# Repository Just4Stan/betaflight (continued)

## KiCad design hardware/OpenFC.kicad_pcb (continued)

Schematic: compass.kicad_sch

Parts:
C113: 100n; C_0402_1005Metric; LCSC C1525; not fitted
U31: LIS3MDLTR; LGA-12_L2.0-W2.0-P0.50-BL; LCSC Part C478483; not fitted

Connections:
unnamed: C113.1, U31.4 (C1), U31.5 (Vdd), U31.6 (Vdd_IO), U31.10 (CS)
unnamed: C113.2, U31.3 (GND), U31.9 (SD0/SA1)

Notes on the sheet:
Place far from magnetic interference sources

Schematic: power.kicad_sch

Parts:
C2, C16: 22uF; C_0402_1005Metric; LCSC C105226
C32, C33, C39: 100n; C_0402_1005Metric; LCSC C1525
C35, C37: 4.7uF 50v; C_0805_2012Metric; LCSC C98192
C36: 100nF; C_0402_1005Metric; LCSC C1525
C38, C40, C48: 22uF; C_0603_1608Metric; LCSC C2762594
D1, D4, D5, D7: LED_1_Green; LED_0603_1608Metric; LCSC C2994781
D3, D21: RB161QS-40_C28646385; SOD-882_L1.0-W0.6-RD; LCSC Part C28646385
L3, L4: XRTC303020D4R7MBCA; IND-SMD_L3.0-W3.0_AFE303020S; LCSC Part C39846837
Q1: DMN1150UFB-7B; DFN-3L_L1.0-W0.6-P0.65-BR; LCSC Part C459538
R4: 30R; R_0402_1005Metric; LCSC C138007
R7, R14, R16: 100k; R_0402_1005Metric; LCSC C60491
R8: 39k; R_0402_1005Metric; LCSC C137995
R12, R15: 200R; R_0402_1005Metric; LCSC C25087
R19: 10k; R_0402_1005Metric; LCSC C25087
R28: 5.23k; R_0402_1005Metric; LCSC C2684530
R29: 470; R_0402_1005Metric; LCSC C114877
R31: 13.7k; R_0402_1005Metric; LCSC C2933072
U6, U7: LMR51420YDDCR; SOT-23-6_L2.9-W1.6-P0.95-LS2.9-BL; LCSC Part C5383002
U13: TPS746-3.3DRV; WSON-6-1EP_2x2mm_P0.65mm_EP1x1.6mm; LCSC C2868202
U21: NCV8187AMT180TAG; WDFN-6_L2.0-W2.0-P0.65-BL-EP; LCSC Part C893189
U33: TPS2116DRLR; SOT-583-8_L2.1-W1.6-P0.50-LS1.6-BL; LCSC Part C3235557

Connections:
+1.8V_GYRO: C2.1, U21.5 (SNS), U21.6 (OUT); also elsewhere on the board
+3.3V: C16.1, R4.1, U13.1 (OUT); also elsewhere on the board
+5V: C32.1, C33.1, C48.1, D3.1 (C), R12.1, R19.1, U13.4 (EN), U13.6 (IN), U21.1 (IN), U21.2 (EN), U33.2 (VOUT), U33.7 (VOUT); also elsewhere on the board
+5V_BUCK: C40.1, D3.2 (A), L4.2, R7.1, R15.1, R16.2, U33.3 (VIN1), U33.5 (MODE); also elsewhere on the board
+5V_USB: U33.6 (VIN2); also elsewhere on the board
+12V: C38.1, L3.2, R14.2, R29.1; also elsewhere on the board
+BATT: C35.1, C37.1, D21.1 (C), U6.3 (VIN), U6.5 (EN), U7.3 (VIN), U7.5 (EN); also elsewhere on the board
/POWER/1.8V_PG: Q1.1 (G), R19.2, U21.4 (PG)
GND: C2.2, C16.2, C32.2, C33.2, C35.2, C37.2, C38.2, C40.2, C48.2, D1.1 (K), D4.1 (K), D5.1 (K), D21.2 (A), Q1.2 (S), R8.2, R28.2, R31.2, U6.1 (GND), U7.1 (GND), U13.3 (GND), U13.5 (PG), U13.7 (EP), U21.3 (GND), U21.7 (EP), U33.1 (GND); also elsewhere on the board
unnamed: D1.2 (A), R15.2
unnamed: D4.2 (A), R4.2
unnamed: D5.2 (A), R29.2
unnamed: D7.2 (A), R12.2
unnamed: D7.1 (K), Q1.3 (D)
unnamed: C36.2, U6.6 (CB)
unnamed: R14.1, R28.1, U6.4 (FB)
unnamed 103: C36.1, L3.1, U6.2 (SW); also elsewhere on the board
unnamed: C39.2, U7.6 (CB)
unnamed: R16.1, R31.1, U7.4 (FB)
unnamed 106: C39.1, L4.1, U7.2 (SW); also elsewhere on the board
unnamed: R7.2, R8.1, U33.4 (PR1)

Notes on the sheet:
10V
3.3V 1A LDO
1.8V 150mA LDO (high PSRR)
5V Power MUX
Switches up to 4A (TPS2117) from +5V_USB or +5V_BUCK to +5V. Prefers buck over USB, threshold voltage is about 3.5V. The threshold voltage is low to prevent accidental switchover to USB during peak consumption (worst case in flight). Emergency diode for if that happens during flight.

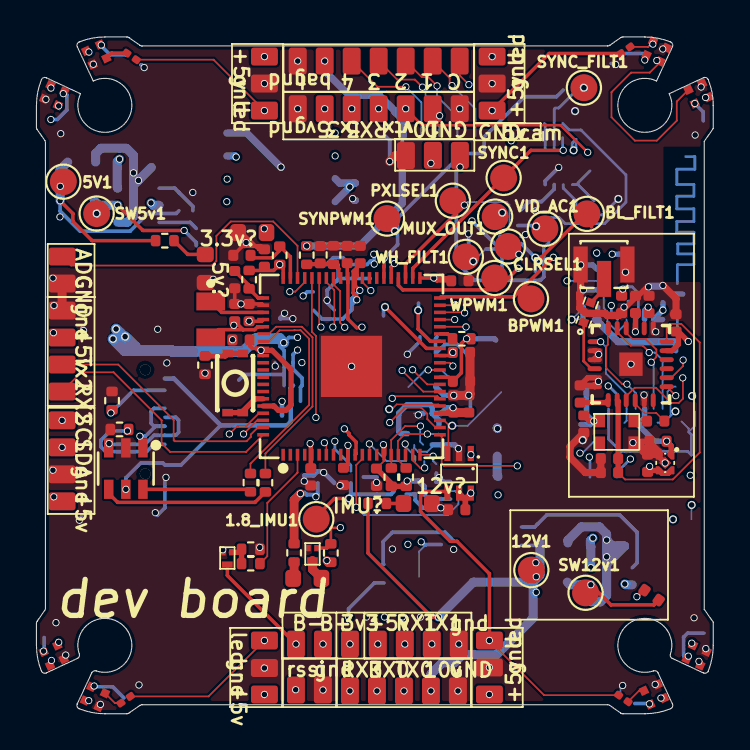
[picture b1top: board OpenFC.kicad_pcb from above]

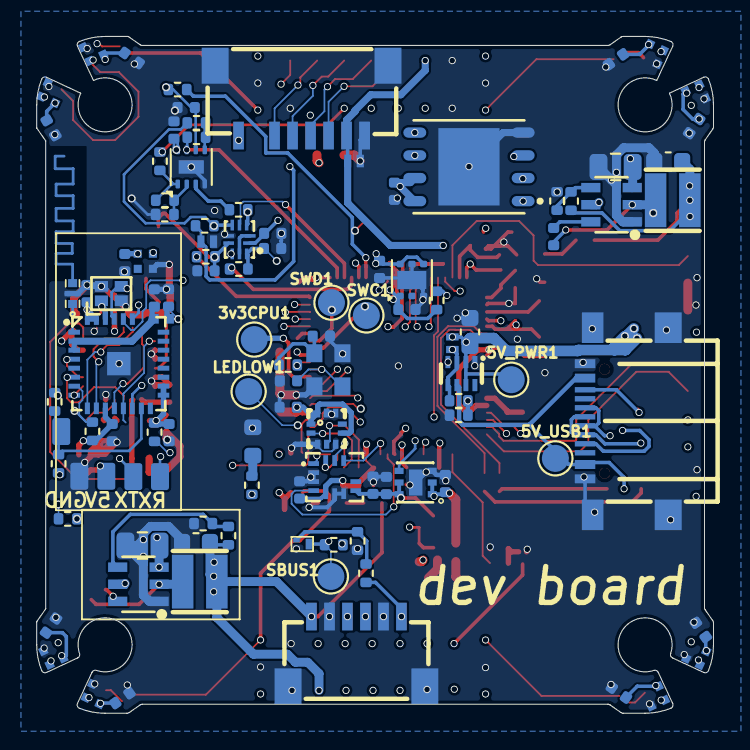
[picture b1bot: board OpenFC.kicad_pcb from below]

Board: 8 copper layers, 37.6 x 37.6 mm, 253 parts (108 on the bottom side), 131 nets.

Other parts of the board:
1.8_IMU1, 3v3CPU1, 5V1, 5V_PWR1, 5V_USB1, 12V1: TestPoint; TestPoint_Pad_D1.5mm
BL_FILT1: TestPoint; TestPoint_Pad_D1.5mm
BPWM1: TestPoint; TestPoint_Pad_D1.5mm
CLRSEL1: TestPoint; TestPoint_Pad_D1.5mm
LEDLOW1: TestPoint; TestPoint_Pad_D1.5mm
MUX_OUT1: TestPoint; TestPoint_Pad_D1.5mm
PXLSEL1: TestPoint; TestPoint_Pad_D1.5mm
SBUS1: TestPoint; TestPoint_Pad_D1.5mm
SW5v1, SW12v1: TestPoint; TestPoint_Pad_D1.5mm
SWC1: TestPoint; TestPoint_Pad_D1.5mm
SWD1: TestPoint; TestPoint_Pad_D1.5mm
SYNC1: TestPoint; TestPoint_Pad_D1.5mm
SYNC_FILT1: TestPoint; TestPoint_Pad_D1.5mm
SYNPWM1: TestPoint; TestPoint_Pad_D1.5mm
VID_AC1: TestPoint; TestPoint_Pad_D1.5mm
WH_FILT1: TestPoint; TestPoint_Pad_D1.5mm
WPWM1: TestPoint; TestPoint_Pad_D1.5mm

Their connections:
+1.8V_GYRO: 1.8_IMU1.1; also elsewhere on the board
+3.3V: 3v3CPU1.1; also elsewhere on the board
+5V: 5V_PWR1.1; also elsewhere on the board
+5V_BUCK: 5V1.1; also elsewhere on the board
+5V_USB: 5V_USB1.1; also elsewhere on the board
+12V: 12V1.1; also elsewhere on the board
/OSD/OSD_PIXSEL: PXLSEL1.1; also elsewhere on the board
/OSD/OSD_PIX_COLOR: CLRSEL1.1; also elsewhere on the board
/OSD/OSD_SYNCLVL_PWM: SYNPWM1.1; also elsewhere on the board
/OSD/OSD_SYNC_RAW: SYNC1.1; also elsewhere on the board
/OSD/OSD_VBLACK_PWM: BPWM1.1; also elsewhere on the board
/OSD/OSD_VWHITE_PWM: WPWM1.1; also elsewhere on the board
/OSD/VBLACK_FILT: BL_FILT1.1; also elsewhere on the board
/OSD/VID_IN: VID_AC1.1; also elsewhere on the board
/OSD/VID_MUX_OUT: MUX_OUT1.1; also elsewhere on the board
/OSD/VWHITE_FILT: WH_FILT1.1; also elsewhere on the board
/RP2350A/LED_STRIP_L: LEDLOW1.1; also elsewhere on the board
/RP2350A/SBUS_INVERT: SBUS1.1; also elsewhere on the board
unnamed 103: SW12v1.1; also elsewhere on the board
unnamed 106: SW5v1.1; also elsewhere on the board
unnamed 122: SWC1.1; also elsewhere on the board
unnamed 123: SWD1.1; also elsewhere on the board
unnamed 131: SYNC_FILT1.1; also elsewhere on the board

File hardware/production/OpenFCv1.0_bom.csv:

Designator,Footprint,Quantity,Value,LCSC Part #
"C1, C9",0402,2,10nF,C15195
"C10, C11, C111, C12, C13, C14, C15, C18, C19, C2, C20, C24, C25, C26, C27, C28, C29, C30, C31, C32, C33, C34, C4, C41, C42, C44, C45, C46, C47, C49, C5, C50, C51, C52, C53, C54, C55, C56, C57, C58, C60, C69, C71, C75, C76, C8",0402,46,100n,C1525
"C16, C17, C43",0402,3,22uF,C105226
"C21, C22, C23, C6",0402,4,4.7uF,C23733
"C3, C59",0402,2,15p,C441742
"C35, C37",0805,2,4.7uF 50v,C98192
"C36, C39",0402,2,100nF,
"C38, C40, C48",0603,3,22uF,C2762594
C7,0402,1,470nF,C92361
"D1, D4, D5, D8",0603,4,LED_1_Green,C2994781
D2,SOT-23-6_L2.9-W1.6-P0.95-LS2.8-BL,1,USBLC6-2SC6,C7519
"D21, D3",SOD-882_L1.0-W0.6-RD,2,RB161QS-40_C28646385,C28646385
D6,0603,1,LED_1_Green,
"FL1, FL2",FILTER-SMD_4P-L1.0-W0.5-L,2,2450FM07D0034T,C2651081
"J1, J10, J11, J12, J13, J14, J15, J16, J17, J18, J19, J2, J20, J21, J22, J23, J24, J25, J26, J27, J28, J29, J3, J30, J31, J32, J33, J34, J35, J36, J38, J39, J4, J40, J42, J43, J44, J45, J46, J47, J48, J49, J5, J50, J53, J56, J6, J7, J8, J9",small_pad,50,5V,
L1,L0402,1,BLM15AG601SN1D,C76884
L2,IND-SMD_L2.0-W1.6_AOTA-B201610S3R3-101-T,1,AOTA-B201610S3R3-101-T,C42411119
"L3, L4",IND-SMD_L3.0-W3.0_AFE303020S,2,XRTC303020D4R7MBCA,C39846837
L7,L0402,1,LQG15HS2N0S02D,C18216
OSC1,OSC-SMD_4P-L2.0-W1.6-BL_TXC_7Z,1,OW7EL89CENUNFAYLC-52M,C22434896
P1,CONN-TH_SM08B-SRSS-TB-LF-SN,1,SM08B-SRSS-TB(LF)(SN),C160407
Q7,DFN-3L_L1.0-W0.6-P0.65-BR,1,DMN1150UFB-7B,C459538
"R1, R11, R25, R26, R3, R6, R9",0402,7,10k,C2909316
"R10, R34, R36, R37",0402,4,6.8k,
R13,0402,1,1k,C106235
"R14, R16, R5, R50, R7",0402,5,100k,C60491
"R15, R20",0402,2,200R,C25087
"R17, R18",0402,2,22R,
"R19, R21, R4",0402,3,33R,C25105
R2,0402,1,75,C11702
R22,0402,1,30R,
"R23, R24, R44, R45",0402,4,5.1k,C105872
R28,0402,1,5.23k,C2684530
R29,0402,1,470,C114877
R31,0402,1,13.7k,C2933072
R8,0402,1,39k,C137995
RF1,IPEX-SMD_3P-L2.6-W2.6-LS3.0,1,CONUFL001-SMD-T,C22418213
"TP1, TP2, TP3",TestPoint_Pad_D1.0mm,3,TestPoint,
U1,CONN-SMD_SM06B-SRSS-TB-LF-SN,1,SM06B-SRSS-TB(LF)(SN),C160405
U10,WSON-8_L6.0-W5.0-P1.27-TL-EP,1,GD25Q256EWIGR,C6564321
U12,UDFN-4_L1.0-W1.0-P0.65-TL,1,WL9005D4-33,C5357206
"U13, U21",WSON-6-1EP_2x2mm_P0.65mm_EP1x1.6mm,2,TPS746-3.3DRV,
U14,LGA-14_L3.0-W2.5-P0.50-BR,1,LSM6DSV16XTR,C5267406
"U15, U16, U17, U18, U19, U22, U23, U24, U25, U26, U27, U28, U29, U3, U4, U5, U8",LED-SMD_4P-L1.0-W1.0-TL_XL-1010RGBC-WS2812B,17,XL-1010RGBC-WS2812B,C5349953
U2,QFN-32_L5.0-W5.0-P0.50-TL-EP3.7,1,ESP32-C3FH4,C2858491
U20,QFN-24_L4.0-W4.0-P0.50-TL-EP2.6,1,SX1281IMLTRT,C2151551
U30,SENSORM-SMD_BMP388,1,BMP388,C779278
U32,QFN-60_L7.0-W7.0-P0.40-TL-EP3.4,1,RP2354A,C41378174
U33,SOT-583-8_L2.1-W1.6-P0.50-LS1.6-BL,1,TPS2116DRLR,C3235557
U34,SW-SMD_4P-L3.0-W2.0-P0.85-LS3.5,1,TS2306A 240GF MSM 9_C2976675,C2976675
U35,QFN-32-1EP_5x5mm_P0.5mm_EP3.1x3.1mm,1,STM32G431KBUx,C1341901
"U6, U7",SOT-23-6_L2.9-W1.6-P0.95-LS2.9-BL,2,LMR51420YDDCR,C5383002
U9,SC-70-6_L2.0-W1.3-P0.65-LS2.1-BL,1,TXU0101DCKR,C5217868
USB2,USB-TYPE-C-SMD_TYPE-C-16P-QTWT,1,TYPE-C 16P QTWT,C5187472
X3,OSC-SMD_4P-L1.6-W1.2-BL-1,1,OT4EL89CJI-111YLC-12M,C42930209

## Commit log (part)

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2026-04-27 index on master: 3c879a06d Add ESP32 interrupt infrastructure, harden UART driver, and fix opaque resource types (#15064)
2026-04-29 index on openfc/phase1-stack: 9a83e9068 PICO: optional opt-in system-clock overclock via PICO_OVERCLOCK_KHZ
2026-04-29 index on openfc/phase1-stack: bd81793a3 PICO: lockless SPSC core1 ring + multicoreScheduleTask API
2026-04-29 PICO: offload dyn_notch peak detection + freq calc onto core1
    Adds a thin core1-offload path for the two stateless steps of
    dyn_notch_filter:STEP_DETECT_PEAKS and STEP_CALC_FREQUENCIES.
    STEP_WINDOW (which reads the live SDFT state and is racy with the
    gyro-task-side sdftPushBatch) and STEP_UPDATE_FILTERS (which writes the
    biquad coefficients consumed by the gyro filter path) stay on core0.
    When USE_MULTICORE is defined and dynNotchOffloadInit() succeeds in
2026-04-30 PICO: assert core0 affinity for hard-realtime gyro / PID / scheduler paths
    Adds ASSERT_CORE0() at the entry of gyroUpdate(), pidController(), and
    both schedulerInit() + scheduler(), making the "core0 is hard-realtime,
    core1 is best-effort offload" invariant a build-time-checkable contract.
    The macro is provided by a new build/core_affinity.h:
    - on USE_MULTICORE targets it expands to hard_assert(get_core_num() == 0)
    - on every other target it expands to nothing
2026-04-30 index on openfc/phase1-stack: a3f6e3b72 sysid_fft: reject N-mismatch on welch_fft_create singleton
2026-04-30 untracked files on openfc/phase1-stack: a3f6e3b72 sysid_fft: reject N-mismatch on welch_fft_create singleton
